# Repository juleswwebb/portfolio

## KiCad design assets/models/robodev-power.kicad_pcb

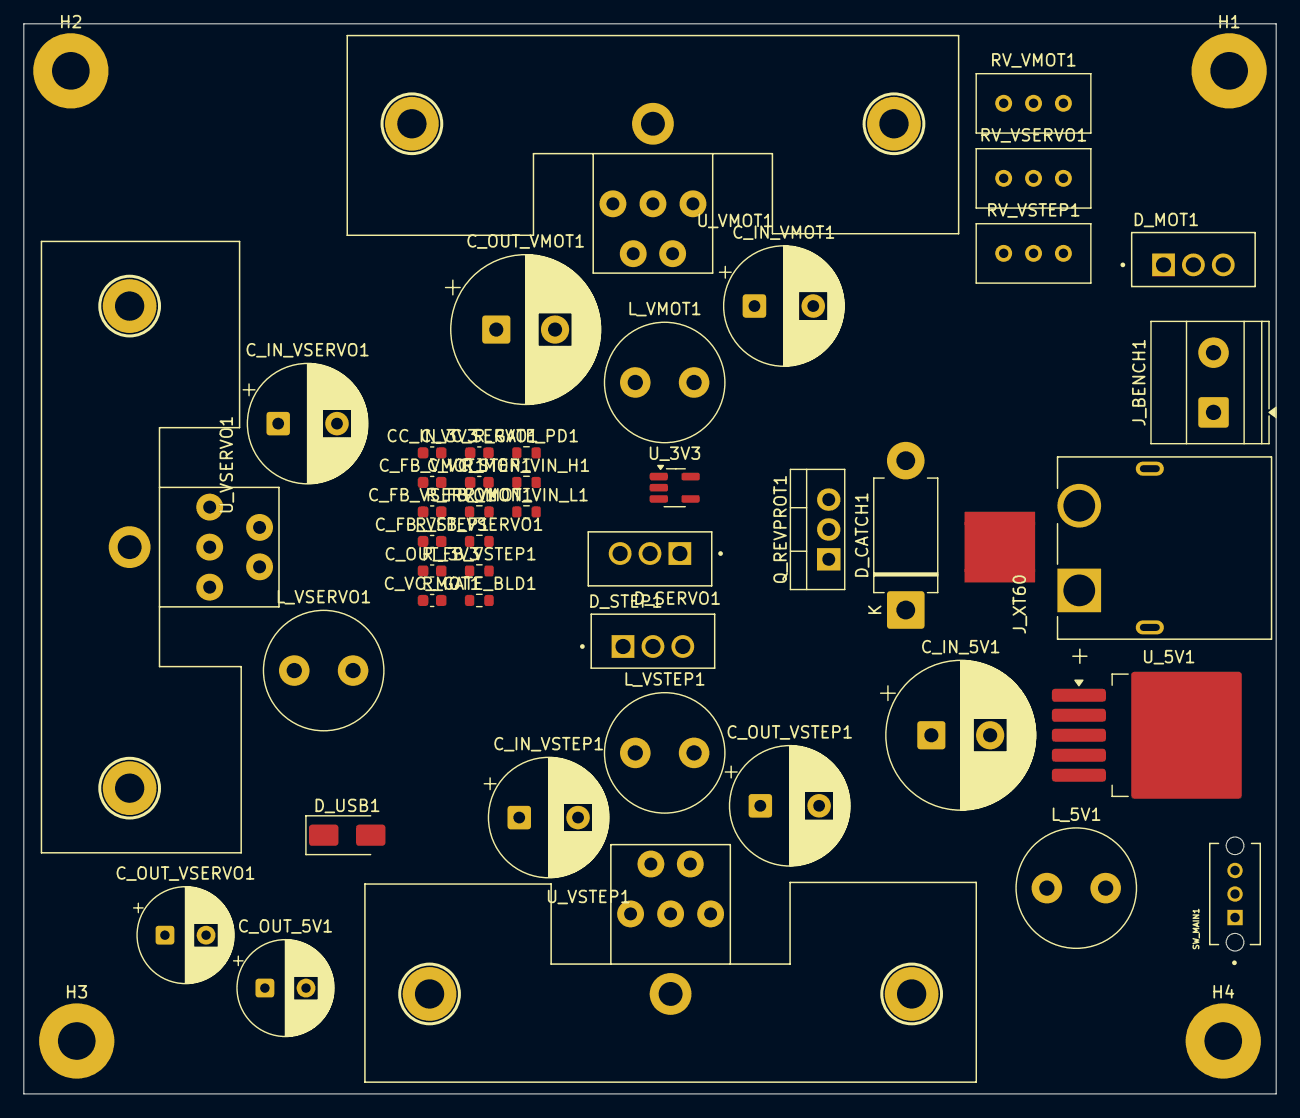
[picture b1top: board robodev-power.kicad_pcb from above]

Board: 4 copper layers, 106.5 x 91.0 mm, 49 parts (0 on the bottom side), 24 nets, no tracks yet.

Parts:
CC_IN_3V3: 1 µF 10 V 0603; C_0603_1608Metric
C_FB_VMOT1: 33 nF 10 V 0603; C_0603_1608Metric
C_FB_VSERVO1: 33 nF 10 V 0603; C_0603_1608Metric
C_FB_VSTEP1: 33 nF 10 V 0603; C_0603_1608Metric
C_IN_5V1: 680 µF 50 V; CP_Radial_D12.5mm_P5.00mm
C_IN_VMOT1: 100 µF 50 V; CP_Radial_D10.0mm_P5.00mm
C_IN_VSERVO1: 100 µF 50 V; CP_Radial_D10.0mm_P5.00mm
C_IN_VSTEP1: 100 µF 50 V; CP_Radial_D10.0mm_P5.00mm
C_OUT_3V3: 1 µF 10 V 0603; C_0603_1608Metric
C_OUT_5V1: 220 µF 10 V; CP_Radial_D8.0mm_P3.50mm
C_OUT_VMOT1: 470 µF 50 V; CP_Radial_D12.5mm_P5.00mm
C_OUT_VSERVO1: 220 µF 25 V; CP_Radial_D8.0mm_P3.50mm
C_OUT_VSTEP1: 100 µF 50 V; CP_Radial_D10.0mm_P5.00mm
C_VC_MOT1: 1 µF ?V 0603; C_0603_1608Metric
C_VC_SERVO1: 1 µF ?V 0603; C_0603_1608Metric
C_VC_STEP1: 1 µF ?V 0603; C_0603_1608Metric
D_CATCH1: 1N5822; D_DO-201AD_P12.70mm_Horizontal
D_MOT1: MBR2045CT; TO254P1050X476X2020-3
D_SERVO1: MBR2045CT; TO254P1050X476X2020-3
D_STEP1: MBR2045CT; TO254P1050X476X2020-3
D_USB1: SS14; D_SMA
H1, H2, H3, H4: MountingHole_Pad; MountingHole_3.2mm_M3_Pad
J_BENCH1: Phoenix MKDS 1.5/2; TerminalBlock_Phoenix_MKDS-1,5-2-5.08_1x02_P5.08mm_Horizont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
J_XT60: XT60PW-M; AMASS_XT60PW-M
L_5V1: 33 µH 4 A; L_Radial_D10.0mm_P5.00mm_Fastron_07M
L_VMOT1: 47 µH 12 A; L_Radial_D10.0mm_P5.00mm_Fastron_07M
L_VSERVO1: 47 µH 12 A; L_Radial_D10.0mm_P5.00mm_Fastron_07M
L_VSTEP1: 47 µH 12 A; L_Radial_D10.0mm_P5.00mm_Fastron_07M
NT1: NetTie_4_Cross; NetTie-4_SMD_Pad2.0mm
Q_REVPROT1: IRF4905; TO-220-3_Vertical
RV_VMOT1: Bourns 3296W 10 kΩ; Potentiometer_Bourns_3296W_Vertical
RV_VSERVO1: Bourns 3296W 10 kΩ; Potentiometer_Bourns_3296W_Vertical
RV_VSTEP1: Bourns 3296W 10 kΩ; Potentiometer_Bourns_3296W_Vertical
R_FB_VMOT1: 100 kΩ 1% 0603; R_0603_1608Metric
R_FB_VSERVO1: 100 kΩ 1% 0603; R_0603_1608Metric
R_FB_VSTEP1: 100 kΩ 1% 0603; R_0603_1608Metric
R_GATE_BLD1: 100 kΩ 1% 0603; R_0603_1608Metric
R_GATE_PD1: 10 kΩ 1% 0603; R_0603_1608Metric
R_MON_VIN_H1: 100 kΩ 1% 0603; R_0603_1608Metric
R_MON_VIN_L1: 10 kΩ 1% 0603; R_0603_1608Metric
SW_MAIN1: OS102011MS2QN1; SW_OS102011MS2QN1
U_3V3: AP2112K-3.3; SOT-23-5_HandSoldering
U_5V1: LM2596HV-5.0; TO-263-5_TabPin3
U_VMOT1: XL4016; LM2576T2
U_VSERVO1: XL4016; LM2576T2
U_VSTEP1: XL4016; LM2576T2

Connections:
+3V3: C_OUT_3V3.1, U_3V3.5 (VOUT)
+5V: CC_IN_3V3.1, C_OUT_5V1.1, D_USB1.1 (K), L_5V1.1, U_3V3.1 (VIN), U_3V3.3 (EN), U_5V1.4 (FB)
/power/ADC_VIN: R_MON_VIN_H1.2, R_MON_VIN_L1.1
/power/VIN: J_BENCH1.1, J_XT60.1, Q_REVPROT1.2 (S), R_GATE_BLD1.1, R_MON_VIN_H1.1
/power/VIN_SWITCHED: C_IN_5V1.1, C_IN_VMOT1.1, C_IN_VSERVO1.1, C_IN_VSTEP1.1, C_VC_MOT1.1, C_VC_SERVO1.1, C_VC_STEP1.1, Q_REVPROT1.3 (D), U_5V1.1 (VIN), U_VMOT1.5 (VIN), U_VSERVO1.5 (VIN), U_VSTEP1.5 (VIN)
/power/VMOT: C_OUT_VMOT1.1, L_VMOT1.2, R_FB_VMOT1.1
/power/VSERVO: C_OUT_VSERVO1.1, L_VSERVO1.2, R_FB_VSERVO1.2
/power/VSTEP: C_OUT_VSTEP1.1, L_VSTEP1.1, R_FB_VSTEP1.1
GND: CC_IN_3V3.2, C_IN_5V1.2, C_IN_VMOT1.2, C_IN_VSERVO1.2, C_IN_VSTEP1.2, C_OUT_3V3.2, C_OUT_5V1.2, D_CATCH1.2 (A), D_MOT1.1, D_MOT1.3, D_SERVO1.1, D_SERVO1.3, D_STEP1.1, D_STEP1.3, H1.1, H2.1, H3.1, H4.1, J_BENCH1.2, J_XT60.2 (N), NT1.3, RV_VMOT1.3, RV_VSERVO1.3, RV_VSTEP1.3, R_GATE_PD1.1, R_MON_VIN_L1.2, U_3V3.2 (GND), U_5V1.3 (GND), U_5V1.5 (~ON/OFF), U_VMOT1.1 (GND), U_VSERVO1.1 (GND), U_VSTEP1.1 (GND)
MGND: C_OUT_VMOT1.2, NT1.1
unnamed: D_CATCH1.1 (K), L_5V1.2, U_5V1.2 (OUT)
unnamed: Q_REVPROT1.1 (G), R_GATE_BLD1.2, SW_MAIN1.1
unnamed: R_GATE_PD1.2, SW_MAIN1.2
unnamed: C_FB_VMOT1.2, RV_VMOT1.2, R_FB_VMOT1.2, U_VMOT1.2 (FB)
unnamed: C_FB_VMOT1.1, D_MOT1.2, L_VMOT1.1, RV_VMOT1.1, U_VMOT1.3 (OUT)
unnamed: C_VC_MOT1.2, U_VMOT1.4 (VC)
unnamed: C_FB_VSERVO1.2, RV_VSERVO1.2, R_FB_VSERVO1.1, U_VSERVO1.2 (FB)
unnamed: C_FB_VSERVO1.1, D_SERVO1.2, L_VSERVO1.1, RV_VSERVO1.1, U_VSERVO1.3 (OUT)
unnamed: C_VC_SERVO1.2, U_VSERVO1.4 (VC)
unnamed: C_FB_VSTEP1.2, RV_VSTEP1.2, R_FB_VSTEP1.2, U_VSTEP1.2 (FB)
unnamed: C_FB_VSTEP1.1, D_STEP1.2, L_VSTEP1.2, RV_VSTEP1.1, U_VSTEP1.3 (OUT)
unnamed: C_VC_STEP1.2, U_VSTEP1.4 (VC)
SERVOGND: C_OUT_VSERVO1.2, NT1.4
STEPGND: C_OUT_VSTEP1.2, NT1.2
